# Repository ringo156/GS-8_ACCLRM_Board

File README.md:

# GS-8_ACCLRM_Board

High range accelerometer board for GS-8

Master project -> [project-arrows/GS-8](https://github.com/project-arrows/GS-8)

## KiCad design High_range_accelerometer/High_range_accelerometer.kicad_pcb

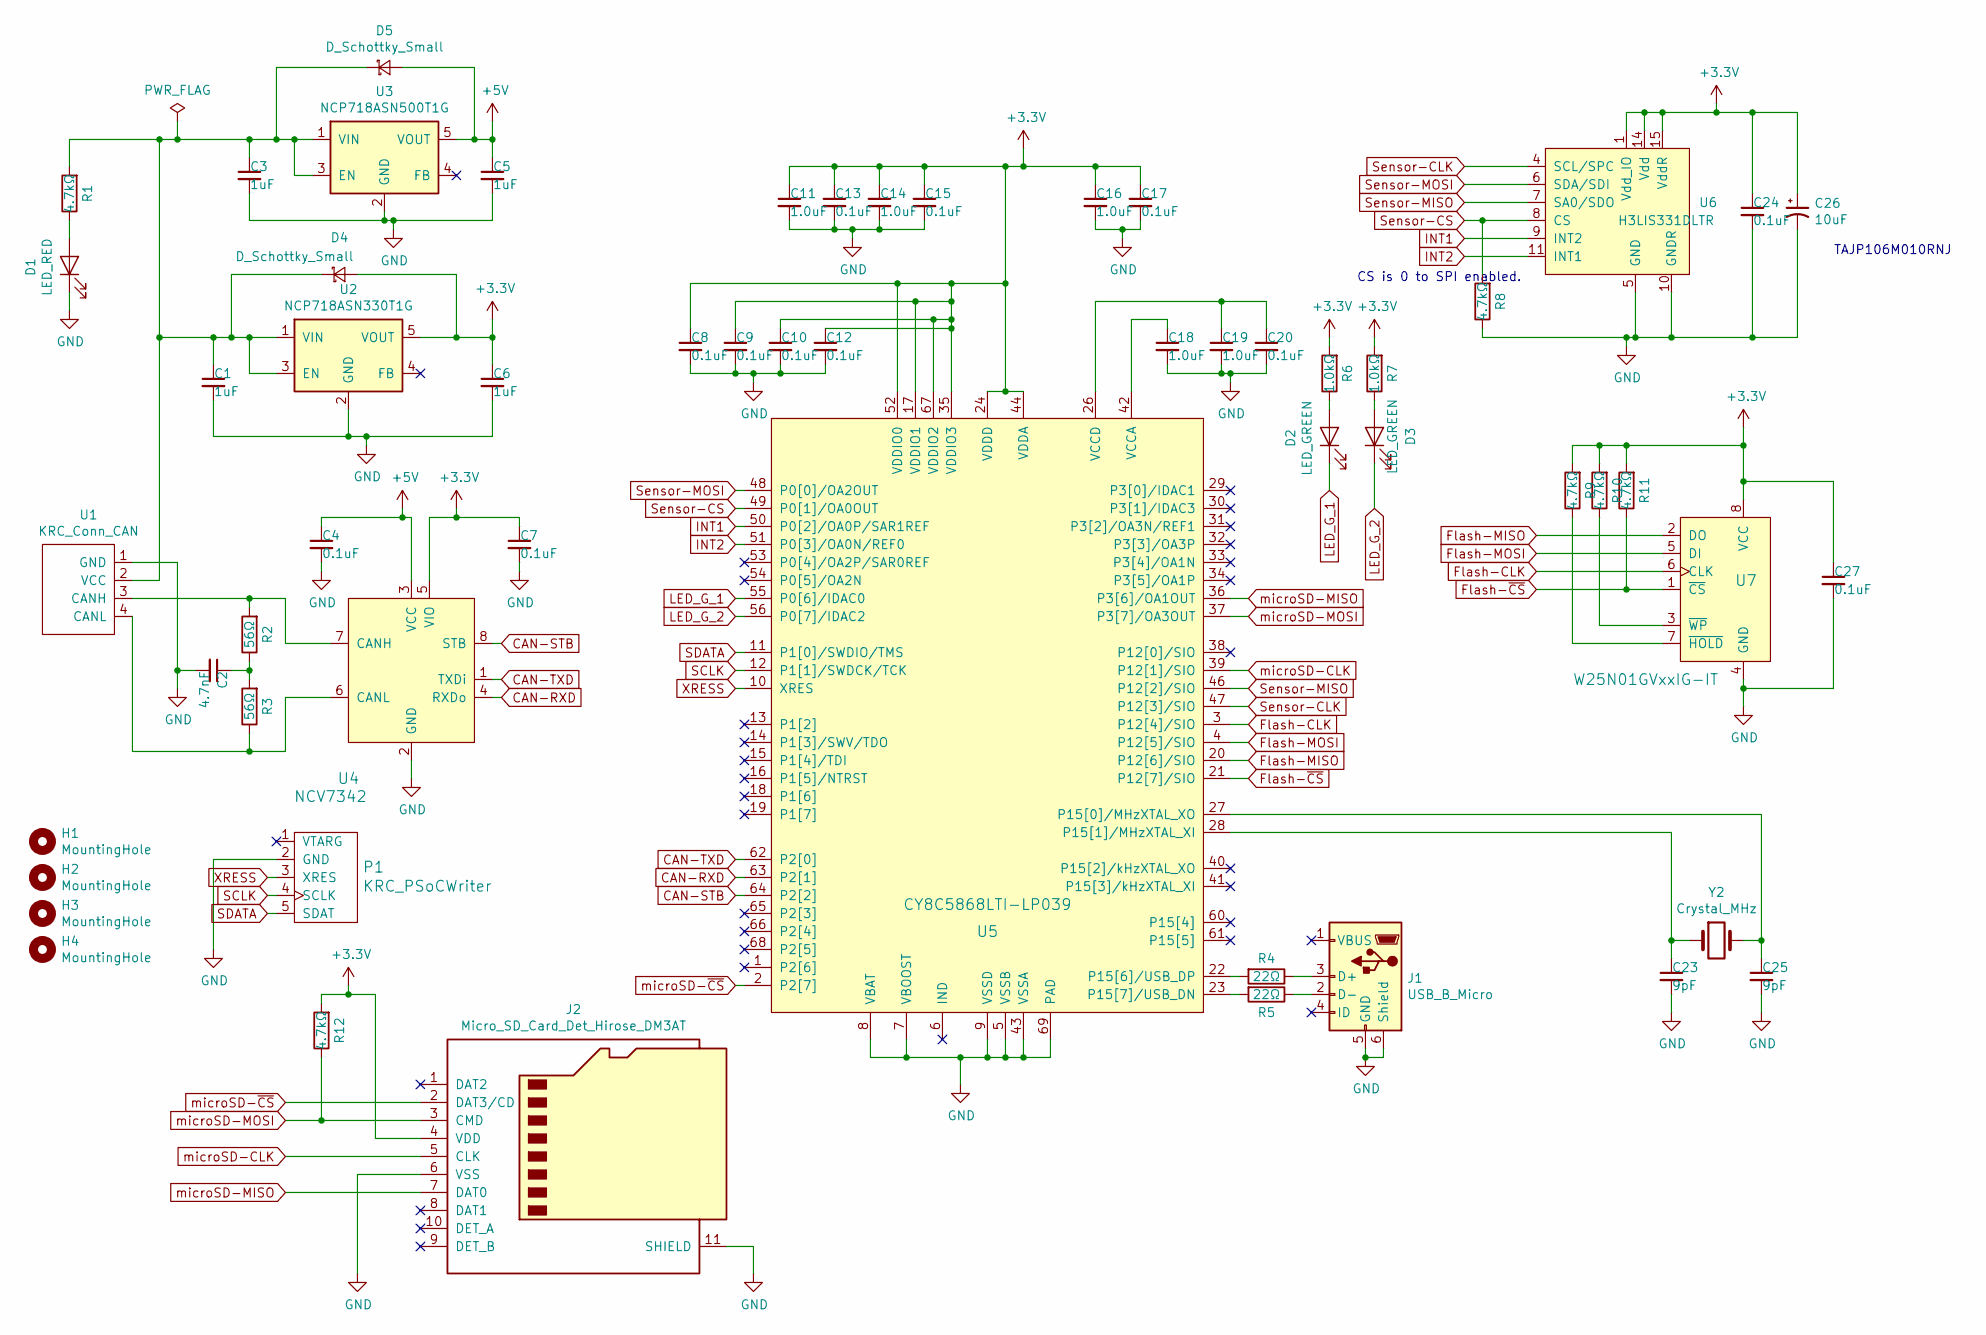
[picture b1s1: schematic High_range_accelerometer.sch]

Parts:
C1, C3, C5, C6: 1uF; C_0402_1005Metric
C2: 4.7nF; C_0402_1005Metric
C4, C7, C8, C9, C10, C12, C13, C15, C17, C20, C24, C27: 0.1uF; C_0402_1005Metric
C11, C14, C16, C18, C19: 1.0uF; C_0402_1005Metric
C23, C25: 9pF; C_0402_1005Metric
C26: 10uF; C_0805_2012Metric
D1: LED_RED; LED_0603_1608Metric
D2, D3: LED_GREEN; LED_0603_1608Metric
D4, D5: D_Schottky_Small; D_0603_1608Metric
H1, H2, H3, H4: MountingHole; MountingHole_3.2mm_M3
J1: USB_B_Micro; Hirose_ZX_ZX62D-B-5P8
J2: Micro_SD_Card_Det_Hirose_DM3AT; microSD_HC_Hirose_DM3AT-SF-PEJM5
P1: KRC_PSoCWriter; JST_JQ_05JQ-BT_1x05_P2.5mm_Vertical
R1, R8, R9, R10, R11, R12: 4.7kΩ; R_0402_1005Metric
R2, R3: 56Ω; R_0402_1005Metric
R4, R5: 22Ω; R_0402_1005Metric
R6, R7: 1.0kΩ; R_0402_1005Metric
U1: KRC_Conn_CAN; JST_XH_S04B-XH-A_1x04_P2.50mm_Horizontal
U2: NCP718ASN330T1G; TSOT-23-5
U3: NCP718ASN500T1G; TSOT-23-5
U4: NCV7342; DFN-8_2x2mm_P0.5mm
U5: CY8C5868LTI-LP039; Cypress_QFN-68_EP_8x8_Pitch0.4mm
U6: H3LIS331DLTR; LGA-16_3x3mm_P0.5mm_LayoutBorder3x5y_handsoldering
U7: W25N01GVxxIG-IT; WSON-8_8x6mm_P1.27mm
Y2: Crystal_MHz; Crystal_Murata_XRCHA

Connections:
+3V3: C6.1, C7.1, C8.1, C9.1, C10.1, C11.1, C12.1, C13.1, C14.1, C15.1, C16.1, C17.1, C24.1, C26.1, C27.1, D4.2 (A), J2.4 (VDD), R6.2, R7.2, R9.2, R10.2, R11.2, R12.2, U2.5 (VOUT), U4.5 (VIO), U5.17 (VDDIO1), U5.24 (VDDD), U5.35 (VDDIO3), U5.44 (VDDA), U5.52 (VDDIO0), U5.59 (VDDD), U5.67 (VDDIO2), U6.1 (Vdd_IO), U6.14 (Vdd), U6.15 (VddR), U7.8 (VCC)
+5V: C4.1, C5.1, D5.2 (A), U3.5 (VOUT), U4.3 (VCC)
CAN-RXD: U4.4 (RXDo), U5.63 (P2[1])
CAN-STB: U4.8 (STB), U5.64 (P2[2])
CAN-TXD: U4.1 (TXDi), U5.62 (P2[0])
Flash-CLK: U5.3 (P12[4]/SIO), U7.6 (CLK)
Flash-MISO: U5.20 (P12[6]/SIO), U7.2 (DO)
Flash-MOSI: U5.4 (P12[5]/SIO), U7.5 (DI)
Flash-~CS: R11.1, U5.21 (P12[7]/SIO), U7.1 (~CS)
GND: C1.2, C2.2, C3.2, C4.2, C5.2, C6.2, C7.2, C8.2, C9.2, C10.2, C11.2, C12.2, C13.2, C14.2, C15.2, C16.2, C17.2, C18.2, C19.2, C20.2, C23.2, C24.2, C25.2, C26.2, C27.2, D1.1 (K), J1.5 (GND), J1.6 (Shield), J2.6 (VSS), J2.11 (SHIELD), P1.2 (GND), R8.1, U1.1 (GND), U2.2 (GND), U3.2 (GND), U4.2 (GND), U5.5 (VSSB), U5.7 (VBOOST), U5.8 (VBAT), U5.9 (VSSD), U5.25 (VSSD), U5.43 (VSSA), U5.45 (VSSD), U5.58 (VSSD), U5.69 (PAD), U6.5 (GND), U6.10 (GNDR), U6.12 (GND), U6.13 (GND), U6.16 (GND), U7.4 (GND)
INT1: U5.50 (P0[2]/OA0P/SAR1REF), U6.9 (INT2)
INT2: U5.51 (P0[3]/OA0N/REF0), U6.11 (INT1)
LED_G_1: D2.1 (K), U5.55 (P0[6]/IDAC0)
LED_G_2: D3.1 (K), U5.56 (P0[7]/IDAC2)
unnamed: C1.1, C3.1, D4.1 (K), D5.1 (K), R1.2, U1.2 (VCC), U2.1 (VIN), U2.3 (EN), U3.1 (VIN), U3.3 (EN)
unnamed: C2.1, R2.1, R3.2
unnamed: C18.1, U5.42 (VCCA)
unnamed: C19.1, C20.1, U5.26 (VCCD), U5.57 (VCCD)
unnamed: C23.1, U5.28 (P15[1]/MHzXTAL_XI), Y2.1
unnamed: C25.1, U5.27 (P15[0]/MHzXTAL_XO), Y2.2
unnamed: D1.2 (A), R1.1
unnamed: D2.2 (A), R6.1
unnamed: D3.2 (A), R7.1
unnamed: J1.2 (D-), R5.1
unnamed: J1.3 (D+), R4.1
unnamed: R2.2, U1.3 (CANH), U4.7 (CANH)
unnamed: R3.1, U1.4 (CANL), U4.6 (CANL)
unnamed: R4.2, U5.22 (P15[6]/USB_DP)
unnamed: R5.2, U5.23 (P15[7]/USB_DN)
unnamed: R9.1, U7.7 (~HOLD)
unnamed: R10.1, U7.3 (~WP)
SCLK: P1.4 (SCLK), U5.12 (P1[1]/SWDCK/TCK)
SDATA: P1.5 (SDAT), U5.11 (P1[0]/SWDIO/TMS)
Sensor-CLK: U5.47 (P12[3]/SIO), U6.4 (SCL/SPC)
Sensor-CS: R8.2, U5.49 (P0[1]/OA0OUT), U6.8 (CS)
Sensor-MISO: U5.46 (P12[2]/SIO), U6.7 (SA0/SDO)
Sensor-MOSI: U5.48 (P0[0]/OA2OUT), U6.6 (SDA/SDI)
XRESS: P1.3 (XRES), U5.10 (XRES)
microSD-CLK: J2.5 (CLK), U5.39 (P12[1]/SIO)
microSD-MISO: J2.7 (DAT0), U5.36 (P3[6]/OA1OUT)
microSD-MOSI: J2.3 (CMD), R12.1, U5.37 (P3[7]/OA3OUT)
microSD-~CS: J2.2 (DAT3/CD), U5.2 (P2[7])

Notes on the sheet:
CS is 0 to SPI enabled.
TAJP106M010RNJ

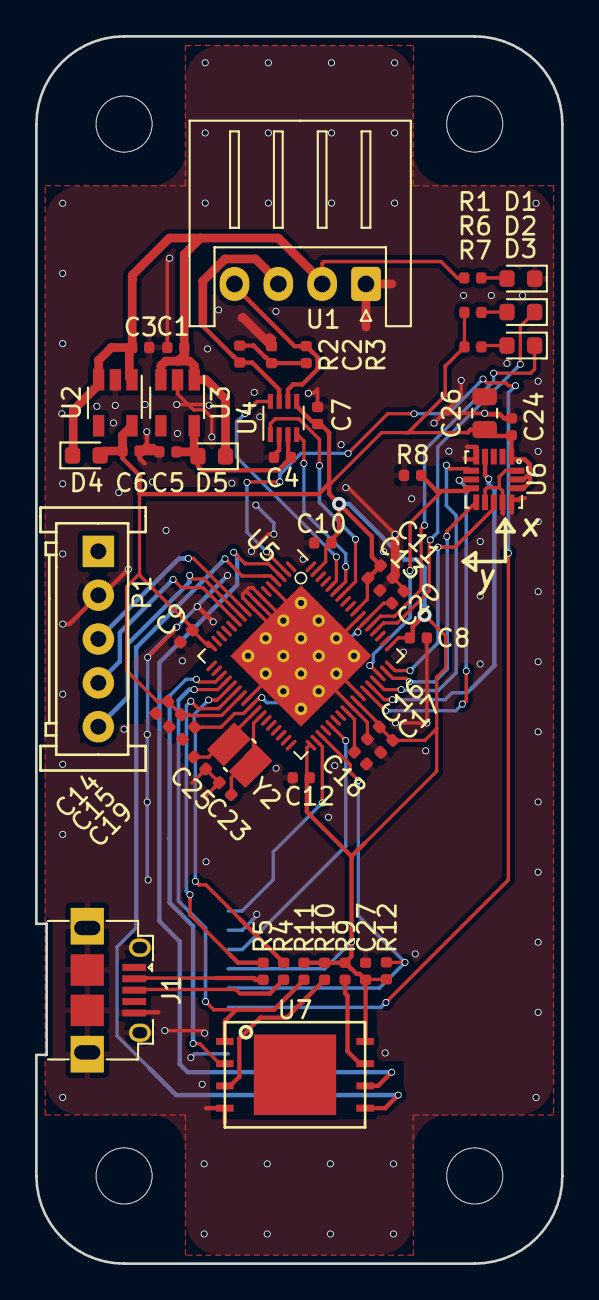
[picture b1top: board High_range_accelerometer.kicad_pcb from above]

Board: 2 copper layers, 30.0 x 70.0 mm, 57 parts (1 on the bottom side), 42 nets.

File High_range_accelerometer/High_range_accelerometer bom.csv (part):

"Source:","C:\Users\Ringo Ohnishi\Documents\kicad\GS-8\High_range_accelerometer\High_range_accelerometer.sch"
"Date:","2019/10/15 12:51:46"
"Tool:","Eeschema (5.0.2)-1"
"Generator:","C:\Program Files\KiCad\bin\scripting\plugins/bom_csv_grouped_by_value.py"
"Component Count:","57"

"Individual Components:"

"Item","Qty","Reference(s)","Value","LibPart","Footprint","Datasheet"
"","","C1","1uF","Device:C_Small","Capacitor_SMD:C_0402_1005Metric","~"
"","","C2","4.7nF","Device:C_Small","Capacitor_SMD:C_0402_1005Metric","~"
"","","C3","1uF","Device:C_Small","Capacitor_SMD:C_0402_1005Metric","~"
"","","C4","0.1uF","Device:C_Small","Capacitor_SMD:C_0402_1005Metric","~"
"","","C5","1uF","Device:C_Small","Capacitor_SMD:C_0402_1005Metric","~"
"","","C6","1uF","Device:C_Small","Capacitor_SMD:C_0402_1005Metric","~"
"","","C7","0.1uF","Device:C_Small","Capacitor_SMD:C_0402_1005Metric","~"
"","","C8","0.1uF","Device:C_Small","Capacitor_SMD:C_0402_1005Metric","~"
"","","C9","0.1uF","Device:C_Small","Capacitor_SMD:C_0402_1005Metric","~"
"","","C10","0.1uF","Device:C_Small","Capacitor_SMD:C_0402_1005Metric","~"
"","","C11","1.0uF","Device:C_Small","Capacitor_SMD:C_0402_1005Metric","~"
"","","C12","0.1uF","Device:C_Small","Capacitor_SMD:C_0402_1005Metric","~"
"","","C13","0.1uF","Device:C_Small","Capacitor_SMD:C_0402_1005Metric","~"
"","","C14","1.0uF","Device:C_Small","Capacitor_SMD:C_0402_1005Metric","~"
"","","C15","0.1uF","Device:C_Small","Capacitor_SMD:C_0402_1005Metric","~"
"","","C16","1.0uF","Device:C_Small","Capacitor_SMD:C_0402_1005Metric","~"
"","","C17","0.1uF","Device:C_Small","Capacitor_SMD:C_0402_1005Metric","~"
"","","C18","1.0uF","Device:C_Small","Capacitor_SMD:C_0402_1005Metric","~"
"","","C19","1.0uF","Device:C_Small","Capacitor_SMD:C_0402_1005Metric","~"
"","","C20","0.1uF","Device:C_Small","Capacitor_SMD:C_0402_1005Metric","~"
"","","C23","9pF","Device:C_Small","Capacitor_SMD:C_0402_1005Metric","~"
"","","C24","0.1uF","Device:C_Small","Capacitor_SMD:C_0402_1005Metric","~"
"","","C25","9pF","Device:C_Small","Capacitor_SMD:C_0402_1005Metric","~"
"","","C26","10uF","Device:CP1_Small","Capacitor_SMD:C_0805_2012Metric","~"
"","","C27","0.1uF","Device:C_Small","Capacitor_SMD:C_0402_1005Metric","~"
"","","D1","LED_RED","Device:LED","LED_SMD:LED_0603_1608Metric","~"
"","","D2","LED_GREEN","Device:LED","LED_SMD:LED_0603_1608Metric","~"
"","","D3","LED_GREEN","Device:LED","LED_SMD:LED_0603_1608Metric","~"
"","","D4","D_Schottky_Small","Device:D_Schottky_Small","Diode_SMD:D_0603_1608Metric","~"
"","","D5","D_Schottky_Small","Device:D_Schottky_Small","Diode_SMD:D_0603_1608Metric","~"
"","","H1","MountingHole","Mechanical:MountingHole","MountingHole:MountingHole_3.2mm_M3","~"
"","","H2","MountingHole","Mechanical:MountingHole","MountingHole:MountingHole_3.2mm_M3","~"
"","","H3","MountingHole","Mechanical:MountingHole","MountingHole:MountingHole_3.2mm_M3","~"
"","","H4","MountingHole","Mechanical:MountingHole","MountingHole:MountingHole_3.2mm_M3","~"
"","","J1","USB_B_Micro","Connector:USB_B_Micro","KUTKiCad_footprint:Hirose_ZX_ZX62D-B-5P8","~"
"","","J2","Micro_SD_Card_Det_Hirose_DM3AT","Connector:Micro_SD_Card_Det_Hirose_DM3AT","Connector_Card:microSD_HC_Hirose_DM3AT-SF-PEJM5","https://www.hirose.com/product/en/download_file/key_name/DM3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"
"","","P1","KRC_PSoCWriter","High_range_accelerometer-rescue:KRC_PSoCWriter-KUT_Connector","KUTKiCad_footprint:JST_JQ_05JQ-BT_1x05_P2.5mm_Vertical",""
"","","R1","4.7kΩ","Device:R","Resistor_SMD:R_0402_1005Metric","~"
"","","R2","56Ω","Device:R","Resistor_SMD:R_0402_1005Metric","~"
"","","R3","56Ω","Device:R","Resistor_SMD:R_0402_1005Metric","~"
"","","R4","22Ω","Device:R","Resistor_SMD:R_0402_1005Metric","~"
"","","R5","22Ω","Device:R","Resistor_SMD:R_0402_1005Metric","~"
"","","R6","1.0kΩ","Device:R","Resistor_SMD:R_0402_1005Metric","~"
"","","R7","1.0kΩ","Device:R","Resistor_SMD:R_0402_1005Metric","~"
"","","R8","4.7kΩ","Device:R","Resistor_SMD:R_0402_1005Metric","~"
"","","R9","4.7kΩ","Device:R","Resistor_SMD:R_0402_1005Metric","~"
"","","R10","4.7kΩ","Device:R","Resistor_SMD:R_0402_1005Metric","~"
"","","R11","4.7kΩ","Device:R","Resistor_SMD:R_0402_1005Metric","~"
"","","R12","4.7kΩ","Device:R","Resistor_SMD:R_0402_1005Metric","~"
"","","U1","KRC_Conn_CAN","KUTKiCad_symbol:KRC_Conn_CAN","Connector_JST:JST_XH_S04B-XH-A_1x04_P2.50mm_Horizontal",""
"","","U2","NCP718ASN330T1G","Regulator_Linear:ADP7142AUZJ","Package_TO_SOT_SMD:TSOT-23-5","http://www.analog.com/media/en/technical-documentation/data-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"
"","","U3","NCP718ASN500T1G","Regulator_Linear:ADP7142AUZJ","Package_TO_SOT_SMD:TSOT-23-5","http://www.analog.com/media/en/technical-documentation/data-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"
"","","U4","NCV7342","KUTKiCad_symbol:NCV7342","Package_DFN_QFN:DFN-8_2x2mm_P0.5mm",""
"","","U5","CY8C5868LTI-LP039","High_range_accelerometer-rescue:CY8C5868LTI-LP039-KUTKiCad_symbol","KUTKiCad_footprint:Cypress_QFN-68_EP_8x8_Pitch0.4mm",""
"","","U6","H3LIS331DLTR","High_range_accelerometer-rescue:H3LIS331DLTR-My_Library","Package_LGA:LGA-16_3x3mm_P0.5mm_LayoutBorder3x5y","https://www.st.com/content/ccc/resource/technical/document/d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"
"","","U7","W25N01GVxxIG-IT","KUTKiCad_symbol:W25N01GVxxIG-IT","KUTKiCad_footprint:WSON-8_8x6mm_P1.27mm",""
"","","Y2","Crystal_MHz","Device:Crystal","KUTKiCad_footprint:Crystal_Murata_XRCHA","~"



"Collated Components:"

"Item","Qty","Reference(s)","Value","LibPart","Footprint","Datasheet"
"1","4","C1, C3, C5, C6","1uF","Device:C_Small","Capacitor_SMD:C_0402_1005Metric","~"
"2","1","C2","4.7nF","Device:C_Small","Capacitor_SMD:C_0402_1005Metric","~"
"3","12","C4, C7, C8, C9, C10, C12, C13, C15, C17, C20, C24, C27","0.1uF","Device:C_Small","Capacitor_SMD:C_0402_1005Metric","~"
"4","5","C11, C14, C16, C18, C19","1.0uF","Device:C_Small","Capacitor_SMD:C_0402_1005Metric","~"
"5","2","C23, C25","9pF","Device:C_Small","Capacitor_SMD:C_0402_1005Metric","~"
"6","1","C26","10uF","Device:CP1_Small","Capacitor_SMD:C_0805_2012Metric","~"
"7","1","D1","LED_RED","Device:LED","LED_SMD:LED_0603_1608Metric","~"
"8","2","D2, D3","LED_GREEN","Device:LED","LED_SMD:LED_0603_1608Metric","~"
"9","2","D4, D5","D_Schottky_Small","Device:D_Schottky_Small","Diode_SMD:D_0603_1608Metric","~"
"10","4","H1, H2, H3, H4","MountingHole","Mechanical:MountingHole","MountingHole:MountingHole_3.2mm_M3","~"
"11","1","J1","USB_B_Micro","Connector:USB_B_Micro","KUTKiCad_footprint:Hirose_ZX_ZX62D-B-5P8","~"
"12","1","J2","Micro_SD_Card_Det_Hirose_DM3AT","Connector:Micro_SD_Card_Det_Hirose_DM3AT","Connector_Card:microSD_HC_Hirose_DM3AT-SF-PEJM5","https://www.hirose.com/product/en/download_file/key_name/DM3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"
"13","1","P1","KRC_PSoCWriter","High_range_accelerometer-rescue:KRC_PSoCWriter-KUT_Connector","KUTKiCad_footprint:JST_JQ_05JQ-BT_1x05_P2.5mm_Vertical",""
"14","6","R1, R8, R9, R10, R11, R12","4.7kΩ","Device:R","Resistor_SMD:R_0402_1005Metric","~"
"15","2","R2, R3","56Ω","Device:R","Resistor_SMD:R_0402_1005Metric","~"
"16","2","R4, R5","22Ω","Device:R","Resistor_SMD:R_0402_1005Metric","~"
"17","2","R6, R7","1.0kΩ","Device:R","Resistor_SMD:R_0402_1005Metric","~"
"18","1","U1","KRC_Conn_CAN","KUTKiCad_symbol:KRC_Conn_CAN","Connector_JST:JST_XH_S04B-XH-A_1x04_P2.50mm_Horizontal",""
"19","1","U2","NCP718ASN330T1G","Regulator_Linear:ADP7142AUZJ","Package_TO_SOT_SMD:TSOT-23-5","http://www.analog.com/media/en/technical-documentation/data-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"
"20","1","U3","NCP718ASN500T1G","Regulator_Linear:ADP7142AUZJ","Package_TO_SOT_SMD:TSOT-23-5","http://www.analog.com/media/en/technical-documentation/data-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"
"21","1","U4","NCV7342","KUTKiCad_symbol:NCV7342","Package_DFN_QFN:DFN-8_2x2mm_P0.5mm",""
"22","1","U5","CY8C5868LTI-LP039","High_range_accelerometer-rescue:CY8C5868LTI-LP039-KUTKiCad_symbol","KUTKiCad_footprint:Cypress_QFN-68_EP_8x8_Pitch0.4mm",""
"23","1","U6","H3LIS331DLTR","High_range_accelerometer-rescue:H3LIS331DLTR-My_Library","Package_LGA:LGA-16_3x3mm_P0.5mm_LayoutBorder3x5y","https://www.st.com/content/ccc/resource/technical/document/d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"
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
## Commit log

2019-10-07 Update LICENSE
2019-10-08 とりあえずできた
2019-10-08 change regulator
2019-10-08 Add ignore pattern
2019-10-08 Remove ignore files
2019-10-12 organize files
2019-10-12 add extension change script for kicad to elecrow
2019-10-12 add SVG and PDF and Gerber files
2019-10-12 add sdCard
2019-10-12 add picture
2019-10-12 Typo corrected
2019-10-29 modified sensor footprint
